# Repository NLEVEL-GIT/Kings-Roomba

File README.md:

# Kings Roomba

    Kings Roomba isnt a Roomba (shocking).
    Kings Roomba is just a simple remote controlled robot that looks like a Roomba cuz i suck at 3d modeling and has a ultrasonic sensor.

## Features:
    - 4 Wheels - Robot
    - Ultrasonic Sensor - Robot
    - KINGS BRAND FROM HOLLOW KNIGHT - Robot
    - 3000mah Battery (Around 3-4 hours of continuous use) - Robot
    - TFT Display - Controller
    - Joysticks for full control of both wheel groups - Controller
    - 400mah Battery (Still like 3 hours of use) - Controller
    - LIL TENNA (Delarune Reference??????)
    - HORNET AND HER NEEDLE - Controller

## Robot Model:
    Everything fits together using Screws and Brass inserts. It uses M2, M2.5 and M3 Screws and Inserts
    It has a bazzilion pieces including:
    - Main Body
    - Middle Plate
    - Top Plate
    - Whells x 4
    - Brackets x 4

Made in Fusion360. Cuz i am broke and its freee

## Controller Model
    Its less stuff to digest then the actual robot, only needing 3 parts and a couple of Brass inserts and screws.
    The only parts you need are:
    - Bottom Piece
    - Top Piece
    - LIL TENNA (optional)

    LIL TENNA might be optional but dont you dare not print it!!

## PCB AND SCHEMATIC
    IT DONT GOT ONE AND IT DONT NEED ONE CUZ I KNOW WHAT I GOT!!
    in other words you only need a few dupon wires to build it, all parts are either screwed together or lodged in their one nifty room so no need to worry about them getting loose.

## Firmware Overview
    Its Just ArduinoIDE ig.

    - The Screen is to display wether the motor are spinning to the front or back
    - Both ESP talk together using ESP NOW

## BOM:
    Here should be everything you need to make this one of a kinda Kings Roomba to clean up your White Palace Runs

    - 2x Xiao ESP32 S3
    - 1x 1.3 inch TFT Display
    - 1x Keystudio Motor Driver
    - 2x Joystick Modules
    - 4x DC Motors
    - 1x Ultrasonic Senor (HC-SR04)
    - 1x 3000mah 18650 Cell
    - 1x Cell Holder
    - 1x 400mah Lipo Battery
    - 2x Switches
    - Brass Inserts
    - 0x PCB cuz it dont need one
    - 14x Printed Pieces

## Extra stuff
 Firstly Thanks for Reaching the end of the READ ME, that means a lot to me.
 This was my 3rd project I did and I am really happy how it turned out.
 One last thanks is to everyone at Stardance and Hackclub who gave me the chance to do this.

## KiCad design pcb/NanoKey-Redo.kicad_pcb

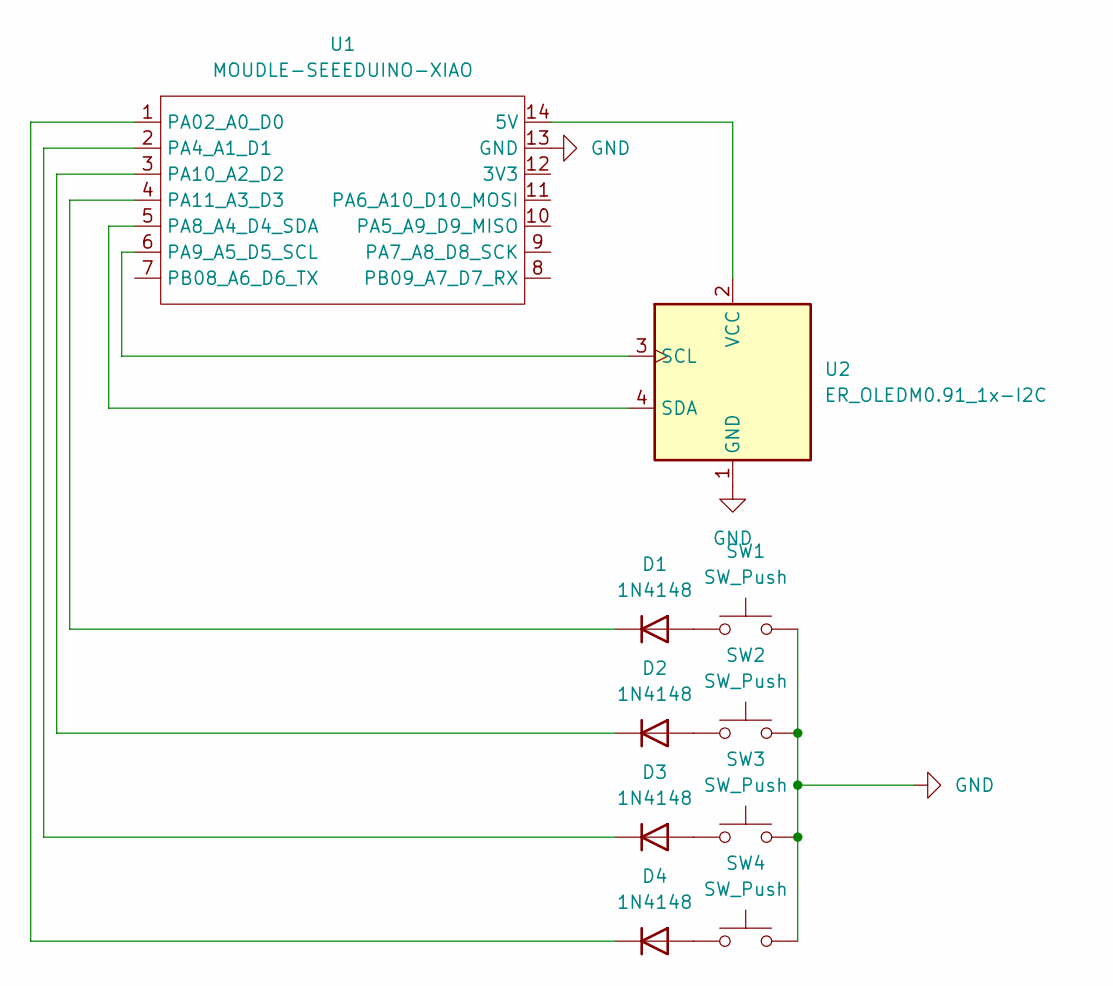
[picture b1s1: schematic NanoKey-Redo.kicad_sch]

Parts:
D1, D2, D3, D4: 1N4148; D_DO-35_SOD27_P7.62mm_Horizontal
SW1, SW2, SW3, SW4: SW_Push; SW_Cherry_MX_1.00u_PCB
U1: MOUDLE-SEEEDUINO-XIAO; XIAO-Generic-Hybrid-14P-2.54-21X17.8MM
U2: ER_OLEDM0.91_1x-I2C

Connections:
GND: SW1.2, SW2.2, SW3.2, SW4.2, U1.13 (GND), U2.1 (GND)
unnamed: D1.2 (A), SW1.1
unnamed: D1.1 (K), U1.4 (PA11_A3_D3)
unnamed: D2.2 (A), SW2.1
unnamed: D2.1 (K), U1.3 (PA10_A2_D2)
unnamed: D3.2 (A), SW3.1
unnamed: D3.1 (K), U1.2 (PA4_A1_D1)
unnamed: D4.2 (A), SW4.1
unnamed: D4.1 (K), U1.1 (PA02_A0_D0)
unnamed: U1.14 (5V), U2.2 (VCC)
unnamed: U1.5 (PA8_A4_D4_SDA), U2.4 (SDA)
unnamed: U1.6 (PA9_A5_D5_SCL), U2.3 (SCL)

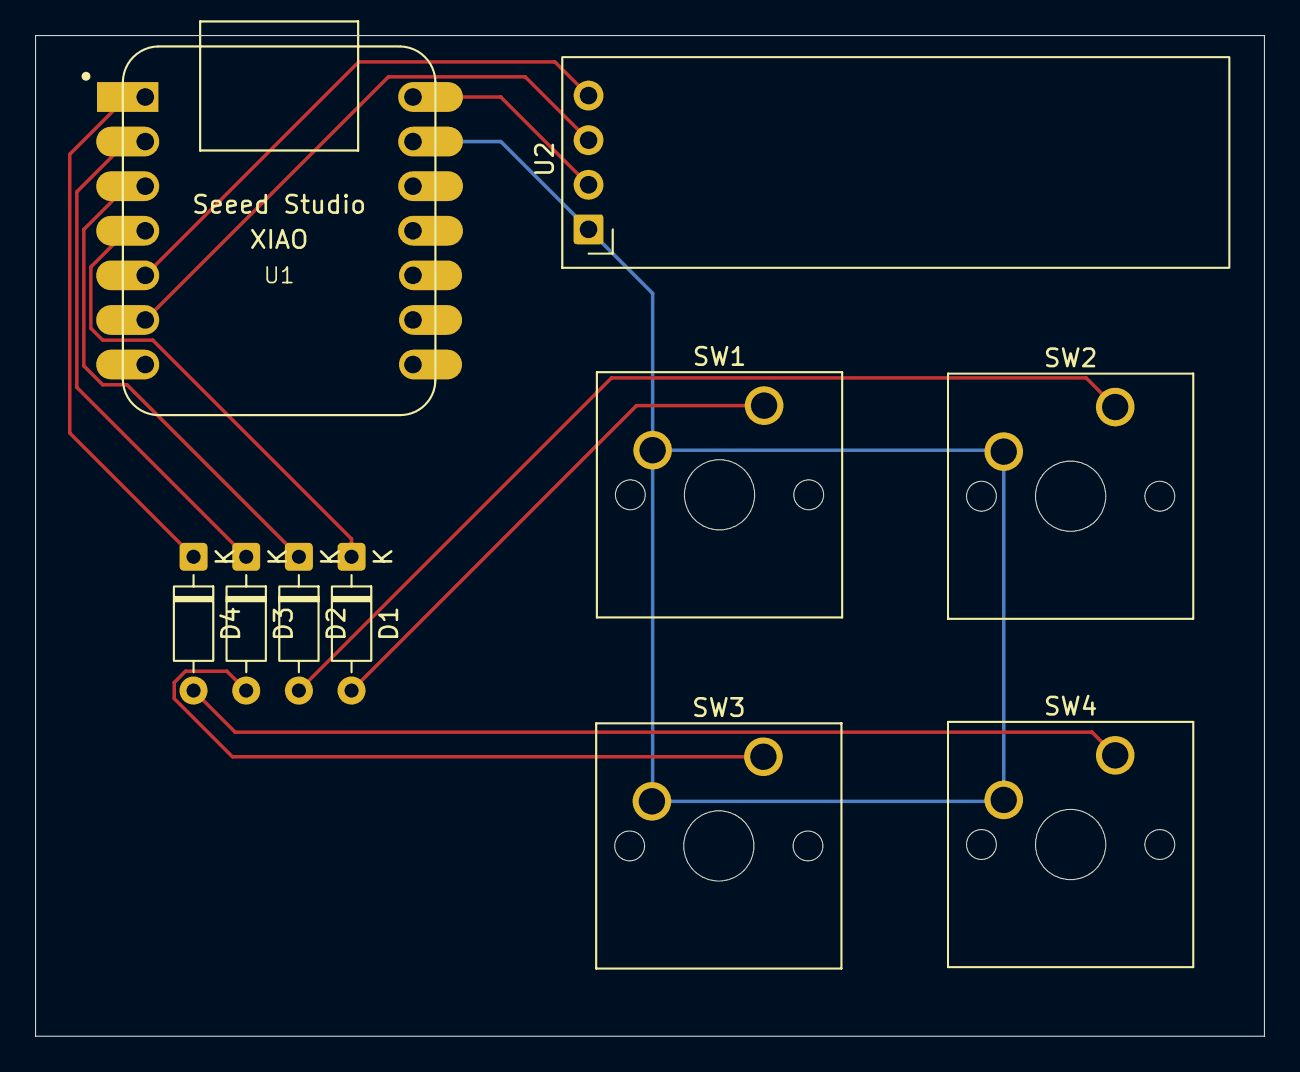
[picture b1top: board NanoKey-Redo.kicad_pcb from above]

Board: 2 copper layers, 70.0 x 57.0 mm, 10 parts (0 on the bottom side), 12 nets.
